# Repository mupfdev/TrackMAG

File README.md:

# TrackMAG

TrackMAG is an open source development board equipped with a
magnetometer, an accelerometer and a gyroscope and it is primarily
intended for the development of accessible input devices.

Details can be found on the [project
website](https://mupfdev.github.io/TrackMAG/).

# License

This project is, unless stated otherwise, licensed under the [CERN Open
Hardware Licence Version 2 -
Permissive](https://ohwr.org/cern_ohl_p_v2.txt).

MotionFX by STMicroelectronics is licenced under the terms of the SLA0077 Software License Agreement.  See the file
[SLA0077.pdf](pdf/SLA0077.pdf) for details.

[webdfu](https://github.com/devanlai/webdfu)</a> by Devan Lai is
licenced under the the [ISC
License](https://github.com/devanlai/webdfu/blob/gh-pages/LICENSE).

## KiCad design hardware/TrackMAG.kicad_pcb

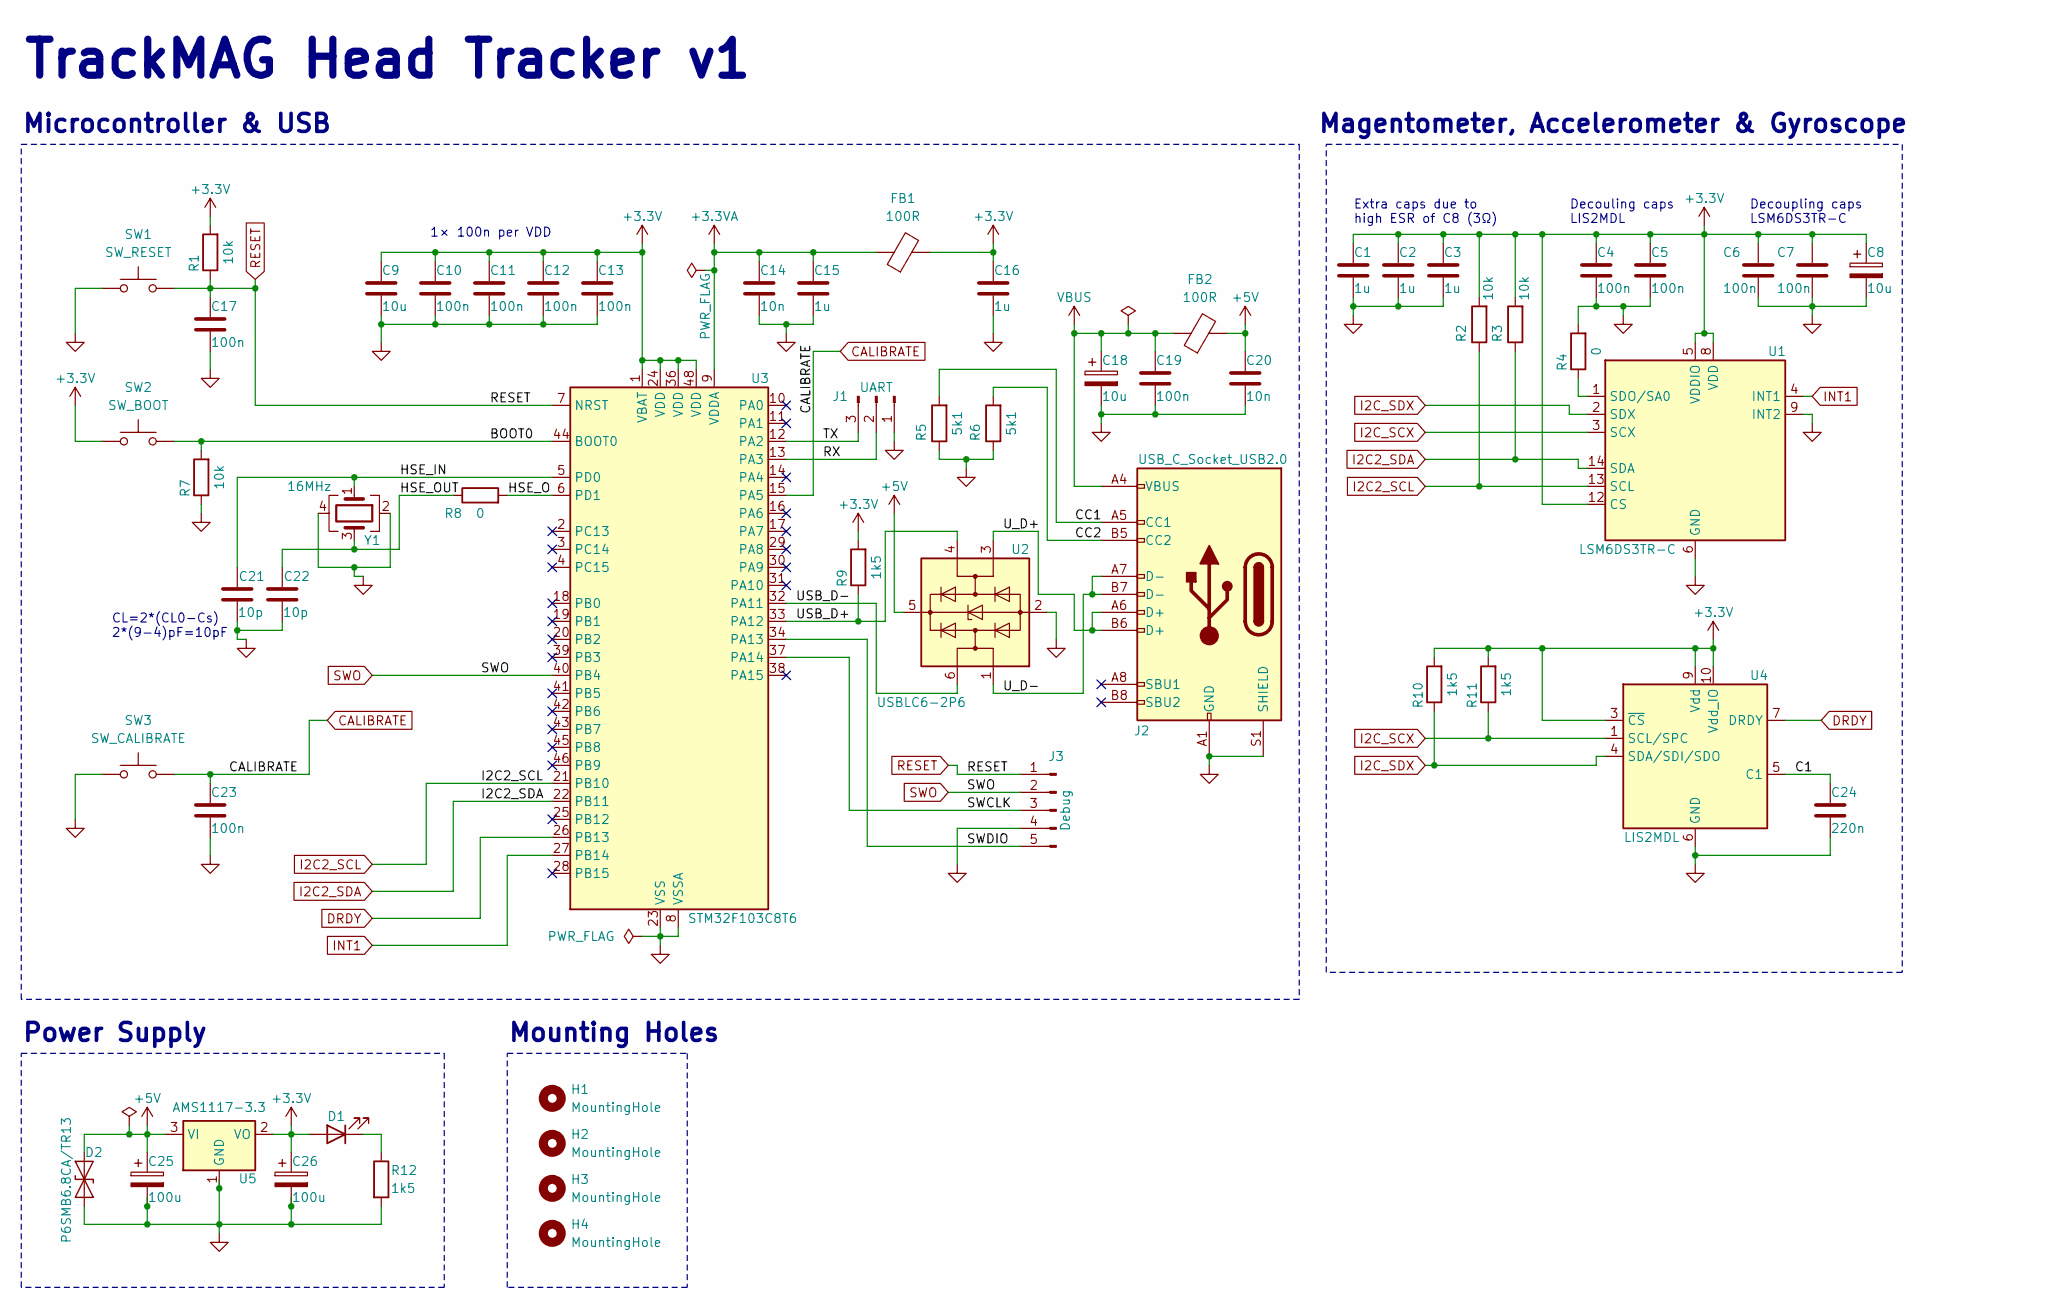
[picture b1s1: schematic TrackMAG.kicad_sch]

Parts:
C1, C2, C3, C15, C16: 1u; C_0402_1005Metric; JLCPCB Part # C52923
C4, C5, C6, C7, C10, C11, C12, C13, C17, C19, C23: 100n; C_0402_1005Metric; JLCPCB Part # C307331
C8, C18: 10u; CP_EIA-3216-18_Kemet-A; JLCPCB Part # C7171
C9: 10u; C_0402_1005Metric; JLCPCB Part # C15525
C14, C20: 10n; C_0402_1005Metric; JLCPCB Part # C15195
C21, C22: 10p; C_0402_1005Metric; JLCPCB Part # C32949
C24: 220n; C_0402_1005Metric; JLCPCB Part # C16772
C25, C26: 100u; CP_EIA-3528-21_Kemet-B; JLCPCB Part # C16133
D1: LED; LED_0603_1608Metric; JLCPCB Part # C2286
D2: P6SMB6.8CA/TR13; D_SMB; JLCPCB Part # C78395
FB1, FB2: 100R; R_0805_2012Metric; JLCPCB Part # C1015
H1, H2, H3, H4: MountingHole; MountingHole_2.1mm
J1: UART; PinHeader_1x03_P2.54mm_UART
J2: USB_C_Socket_USB2.0; USB_C_Receptacle_G-Switch_GT-USB-7010ASV; JLCPCB Part # C2988369
J3: Debug; PinHeader_1x05_P2.54mm_Debug
R1, R2, R3, R7: 10k; R_0402_1005Metric; JLCPCB Part # C25744
R4, R8: 0; R_0402_1005Metric; JLCPCB Part # C17168
R5, R6: 5k1; R_0402_1005Metric; JLCPCB Part # C25905
R9, R10, R11, R12: 1k5; R_0402_1005Metric; JLCPCB Part # C25867
SW1: SW_RESET; SW_Push_1P1T_XKB_TS-1187A_RESET; JLCPCB Part # C318884
SW2: SW_BOOT; SW_Push_1P1T_XKB_TS-1187A_BOOT; JLCPCB Part # C318884
SW3: SW_CALIBRATE; SW_Push_1P1T_XKB_TS-1187A_CALIBRATE; JLCPCB Part # C318884
U1: LSM6DS3TR-C; LGA-14_3x2.5mm_P0.5mm_LayoutBorder3x4y; JLCPCB Part # C967633
U2: USBLC6-2P6; SOT-666; JLCPCB Part # C2827693
U3: STM32F103C8T6; LQFP-48_7x7mm_P0.5mm; JLCPCB Part # C8734
U4: LIS2MDL; LGA-12_2x2mm_P0.5mm; JLCPCB Part # C919695
U5: AMS1117-3.3; SOT-223-3_TabPin2; JLCPCB Part # C6186
Y1: 16MHz; Crystal_SMD_3225-4Pin_3.2x2.5mm; JLCPCB Part # C13738

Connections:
+3.3V: C1.1, C2.1, C3.1, C4.1, C5.1, C6.1, C7.1, C8.1, C9.1, C10.1, C11.1, C12.1, C13.1, C16.1, C26.1, D1.2 (A), FB1.2, R1.2, R2.2, R3.2, R9.2, R10.2, R11.2, SW2.1, U1.5 (VDDIO), U1.8 (VDD), U1.12 (CS), U3.1 (VBAT), U3.24 (VDD), U3.36 (VDD), U3.48 (VDD), U4.3 (~CS), U4.9 (Vdd), U4.10 (Vdd_IO), U5.2 (VO)
+3.3VA: C14.1, C15.1, FB1.1, U3.9 (VDDA)
+5V: C20.1, C25.1, D2.1 (A1), FB2.2, U2.5 (VBUS), U5.3 (VI)
/BOOT0: R7.2, SW2.2, U3.44 (BOOT0)
/C1: C24.1, U4.5 (C1)
/CC1: J2.A5 (CC1), R5.2
/CC2: J2.B5 (CC2), R6.2
/HSE_IN: C21.1, U3.5 (PD0), Y1.1
/HSE_O: R8.2, U3.6 (PD1)
/HSE_OUT: C22.1, R8.1, Y1.3
/RX: J1.2, U3.13 (PA3)
/SWCLK: J3.3, U3.37 (PA14)
/SWDIO: J3.5, U3.34 (PA13)
/TX: J1.3, U3.12 (PA2)
/USB_D+: R9.1, U2.4 (I/O2), U3.33 (PA12)
/USB_D-: U2.6 (I/O1), U3.32 (PA11)
/U_D+: J2.A6 (D+), J2.B6 (D+), U2.3 (I/O2)
/U_D-: J2.A7 (D-), J2.B7 (D-), U2.1 (I/O1)
CALIBRATE: C23.1, SW3.2, U3.15 (PA5)
DRDY: U3.26 (PB13), U4.7 (DRDY)
GND: C1.2, C2.2, C3.2, C4.2, C5.2, C6.2, C7.2, C8.2, C9.2, C10.2, C11.2, C12.2, C13.2, C14.2, C15.2, C16.2, C17.2, C18.2, C19.2, C20.2, C21.2, C22.2, C23.2, C24.2, C25.2, C26.2, D2.2 (A2), J1.1, J2.A1 (GND), J2.A12 (GND), J2.B1 (GND), J2.B12 (GND), J2.S1 (SHIELD), J3.4, R4.2, R5.1, R6.1, R7.1, R12.2, SW1.1, SW3.1, U1.6 (GND), U1.7 (GND), U1.9 (INT2), U2.2 (GND), U3.8 (VSSA), U3.23 (VSS), U3.35 (VSS), U3.47 (VSS), U4.6 (GND), U4.8 (GND), U5.1 (GND), Y1.2, Y1.4
I2C2_SCL: R2.1, U1.13 (SCL), U3.21 (PB10)
I2C2_SDA: R3.1, U1.14 (SDA), U3.22 (PB11)
I2C_SCX: R11.1, U1.3 (SCX), U4.1 (SCL/SPC)
I2C_SDX: R10.1, U1.2 (SDX), U4.4 (SDA/SDI/SDO)
INT1: U1.4 (INT1), U3.27 (PB14)
unnamed: D1.1 (K), R12.1
unnamed: R4.1, U1.1 (SDO/SA0)
RESET: C17.1, J3.1, R1.1, SW1.2, U3.7 (NRST)
SWO: J3.2, U3.40 (PB4)
VBUS: C18.1, C19.1, FB2.1, J2.A4 (VBUS), J2.A9 (VBUS), J2.B4 (VBUS), J2.B9 (VBUS)

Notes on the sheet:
Microcontroller & USB
Power Supply
TrackMAG Head Tracker v1
1× 100n per VDD
CL=2*(CL0-Cs) 2*(9-4)pF=10pF
Decoupling caps LSM6DS3TR-C
Decouling caps LIS2MDL
Magentometer, Accelerometer & Gyroscope
Mounting Holes
Extra caps due to high ESR of C8 (3Ω)

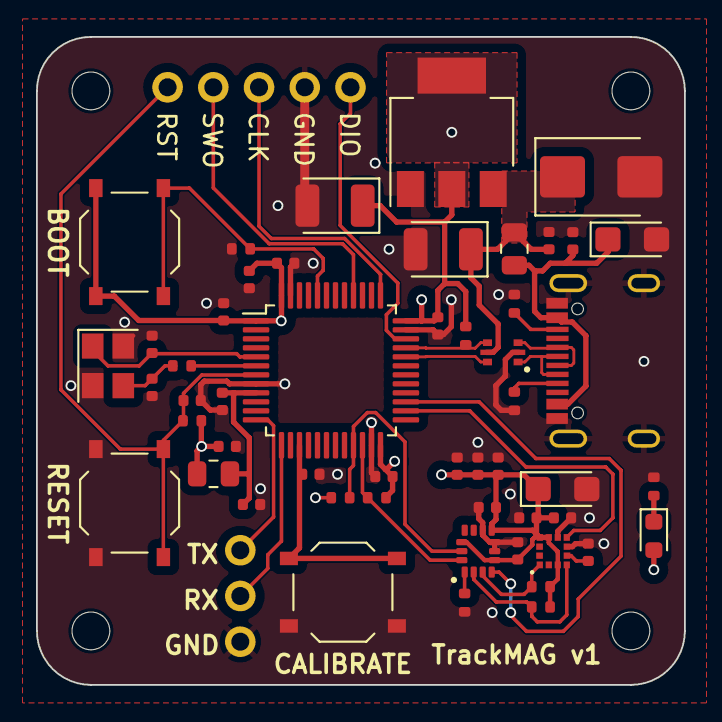
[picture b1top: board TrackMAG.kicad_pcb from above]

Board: 4 copper layers, 36.0 x 36.0 mm, 58 parts (0 on the bottom side), 31 nets.

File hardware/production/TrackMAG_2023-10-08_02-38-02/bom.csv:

Designator,Footprint,Quantity,Value,LCSC Part #
"C1, C15, C16, C2, C3",0402,5,1u,C52923
"C10, C11, C12, C13, C17, C19, C23, C4, C5, C6, C7",0402,11,100n,C307331
"C14, C20",0402,2,10n,C15195
"C18, C8",CP_EIA-3216-18_Kemet-A,2,10u,C7171
"C21, C22",0402,2,10p,C32949
C24,0402,1,220n,C16772
"C25, C26",CP_EIA-3528-21_Kemet-B,2,100u,C16133
C9,0402,1,10u,C15525
D1,0603,1,LED,C2286
D2,D_SMB,1,P6SMB6.8CA,C78395
"FB1, FB2",0805,2,100R,C1015
J2,USB_C_Receptacle_G-Switch_GT-USB-7010ASV,1,USB_C_Socket_USB2.0,C2988369
"R1, R2, R3, R7",0402,4,10k,C25744
"R10, R11, R12, R9",0402,4,1k5,C25867
"R4, R8",0402,2,0,C17168
"R5, R6",0402,2,5k1,C25905 
SW1,SW_Push_1P1T_XKB_TS-1187A_RESET,1,SW_RESET,C318884
SW2,SW_Push_1P1T_XKB_TS-1187A_BOOT,1,SW_BOOT,C318884
SW3,SW_Push_1P1T_XKB_TS-1187A_CALIBRATE,1,SW_CALIBRATE,C318884
U1,LGA-14_3x2.5mm_P0.5mm_LayoutBorder3x4y,1,LSM6DS3TR-C,C967633
U2,SOT-666,1,USBLC6-2P6,C2827693
U3,LQFP-48_7x7mm_P0.5mm,1,STM32F103C8T6,C8734
U4,LGA-12_2x2mm_P0.5mm,1,LIS2MDL,C919695
U5,SOT-223-3_TabPin2,1,AMS1117-3.3,C6186
Y1,Crystal_SMD_3225-4Pin_3.2x2.5mm,1,16MHz, C13738

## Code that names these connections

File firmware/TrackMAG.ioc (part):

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Mcu.Name=STM32F103C(8-B)Tx
Mcu.Package=LQFP48
Mcu.UserName=STM32F103C8Tx
PA11.Mode=Device
PA11.Signal=USB_DM
PA12.Mode=Device
PA12.Signal=USB_DP
PA13.Mode=Serial_Wire
PA13.Signal=SYS_JTMS-SWDIO
PA14.Mode=Serial_Wire
PA14.Signal=SYS_JTCK-SWCLK
PA2.Mode=Asynchronous
PA2.Signal=USART2_TX
PA3.Mode=Asynchronous
PA3.Signal=USART2_RX
PA5.GPIOParameters=GPIO_PuPd,GPIO_Label,GPIO_ModeDefaultEXTI
PA5.GPIO_Label=CALIBRATE
PA5.GPIO_ModeDefaultEXTI=GPIO_MODE_IT_RISING_FALLING
PA5.GPIO_PuPd=GPIO_PULLUP
PA5.Signal=GPXTI5
PB10.Mode=I2C
PB10.Signal=I2C2_SCL
PB11.Mode=I2C
PB11.Signal=I2C2_SDA
PB13.GPIOParameters=GPIO_PuPd,GPIO_Label,GPIO_ModeDefaultEXTI
PB13.GPIO_Label=DRDY
PB13.GPIO_ModeDefaultEXTI=GPIO_MODE_IT_RISING
PB13.GPIO_PuPd=GPIO_PULLDOWN
PB13.Signal=GPXTI13
PB14.GPIOParameters=GPIO_Label,GPIO_ModeDefaultEXTI
PB14.GPIO_Label=INT1
PB14.GPIO_ModeDefaultEXTI=GPIO_MODE_IT_RISING
PB14.Signal=GPXTI14
PD0-OSC_IN.Mode=HSE-External-Oscillator
PD0-OSC_IN.Signal=RCC_OSC_IN
PD1-OSC_OUT.Mode=HSE-External-Oscillator
PD1-OSC_OUT.Signal=RCC_OSC_OUT
RCC.HSEDivPLL=RCC_HSE_PREDIV_DIV2
RCC.HSE_VALUE=16000000
RCC.SYSCLKFreq_VALUE=72000000
RCC.SYSCLKSource=RCC_SYSCLKSOURCE_PLLCLK
board=custom

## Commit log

2023-10-02 Add firmware base project
2023-10-02 Update pinout to match current firmware configuration
2023-10-04 Backup current progress
2023-10-04 Update schematic to match current progress
2023-10-06 Backup currend KiCAD progress
2023-10-06 Add ground planes
2023-10-06 Add missing connections
2023-10-06 Add reference vias
2023-10-06 Cleanup
2023-10-06 Update schematic PDF and minor PCB cleanup
2023-10-06 Center PCB
2023-10-06 Update PDF schematic, add calibrate switch
2023-10-06 Add calibrate switch
2023-10-06 Update base firmware configuration to match current hardware setup
2023-10-07 Fix various problems, cleanup after review
2023-10-07 Minor cleanup
2023-10-07 Remove redundant connection on PB0
2023-10-07 Adjust firmware accordingly, remove setting for PB0
2023-10-07 Remove redundant vias, adjust reference vias
2023-10-07 Optimize PCB layout
2023-10-07 Increase spacing of INT1 line
2023-10-08 Remove UART pin header from position files
2023-10-08 Hide pin header 3D models
2023-10-08 Final cleanup v1
2023-10-08 Add v1 production files used for JLCPCB order
2023-10-11 Minor cleanup, adjust wrong symbol in schematic and adjust TV footprint on PCB
2023-10-11 Add work-in-progress project case
2023-10-12 Add folder: gh-pages
2023-10-12 Move index.html from gh-pages to docs
2023-10-12 Add yet unfinished TrackMAG case to GitHub pages
2023-10-12 Update yet unfinished case 3D model
2023-10-12 Attempt to fix WebGL rendering by fixing load errors
2023-10-12 Move PDFs to dedicated directory, docs is reserved for GitHub pages
2023-10-13 Recreate yet-unfinished case design, lid and snap-fit joint
2023-10-14 Replace snap-fit with simpler press-fit design
2023-10-14 Add yet untested twist-lock for headset mount
2023-10-15 Update mount material for better visibility
2023-10-15 Update project website to fit mupf.dev design
2023-10-15 Update stylesheet links
2023-10-15 Update content type
2023-10-15 Update project description
2023-10-16 Update project website
2023-10-16 Add schematic to project website
2023-10-16 Add basic license
2023-10-16 Add remark regarding flyLILLO ETS
2023-10-18 Add 3D rendering of PCB
2023-10-18 Add missing script
2023-10-18 Add missing html tag
2023-10-18 Enable mobile version of magnifier js
2023-10-18 Update case
2023-10-18 Just making sure everything is up to date
2023-10-19 Optimise case, add buttons
2023-10-19 Add yet unmodified, non-working USB DFU bootloader
2023-10-19 Adjust bootloader vid/pid, update clock configuration to use 16MHz oscillator
2023-10-19 Add webdfu
2023-10-19 Add webdfu.html for testing
2023-10-19 More DFU util debugging
2023-10-19 Add original form code to check whether it is working correctly
2023-10-19 webdfu debugging: remove one thing at a time
2023-10-19 Cosmetic changes, remove redundant button
2023-10-19 Fix error, update vid list
2023-10-19 Fix error?
2023-10-19 bootloader, minor cleanup
2023-10-19 Fix html syntax
2023-10-20 Update index.html: hide Detach DFU button
2023-10-20 Add buttons, minor modifications on case
2023-10-20 Update phrasing
2023-10-20 Update colors for better contrast
2023-10-20 Rework case to be able to strap it to a headset without the optional twist lock mechanism
2023-10-20 Add prototype image
2023-10-20 Add updated model
2023-10-20 Fix path to js, add minimal lightbox script
2023-10-20 Add contents link to prototype section
2023-10-20 Update date
2023-10-20 Prototype: make background transparent
2023-10-20 Replace prototype image because it looks weird, add 3 new images
2023-10-20 Fix typo
2023-10-20 Add css class to gallery
2023-10-20 Update description
2023-10-21 Update phrasing, change licence terms
2023-10-22 Firmware: add basic, XAC-compatible USB-HID support
2023-10-22 Rename HID profile to make clear that it works with the XAC
2023-10-22 Poll sensor data
2023-10-22 Close comment
2023-10-26 Add basic filtering, implement pitch
2023-10-26 Add GitHub actions workflow to build firmware
2023-10-26 Copy workflow to designated directory
2023-10-26 Add status badge
2023-10-26 Update pipeline name
2023-10-26 Fix typos
2023-10-27 Add AN3192
2023-10-27 Add design tip docs by ST
2023-10-28 Remove FreeRTOS, add MotionFX, adjust code accordingly, yet not functional
2023-10-29 Rewrite MAG handler, initialise sensors from scratch, yet unfinished because the calculated yaw axis (MotionFX) seems extremely unstable.
2023-10-30 Apply filter chain
2023-10-30 Disable automatic gbias calculation, calibration only
2023-10-30 Add slightly adjusted linker scripts, setup MotionFX properly - works now, add calibration feature
2023-10-31 Save calibration data to flash, load it on bootup
2023-10-31 Update GitHub actions workflow to patch firmware header (test), minor firmware cleanup
2023-10-31 Fix typo, adjust workflow to only run when the firmware code has been updated
2023-10-31 Update workflow
2023-10-31 Test workflow
2023-10-31 Fix path in workflow
2023-10-31 Adjust file name of output binary
2023-10-31 Adjust binary file name
2023-10-31 Test workflow adjustment
2023-10-31 Adjust workflow
2023-10-31 Fix error in workflow
2023-10-31 Upload firmware binary to project website
2023-10-31 Add link to latest firmware
2023-10-31 Output orientation string via UART
2023-10-31 Add firmware build status badge
2023-10-31 Move badge to status section
2023-10-31 Reorganise
2023-10-31 Update formatting
2023-10-31 Reorganise elements
2023-11-01 Use 0 for default calibration when stored value is not a number, eg when flash is empty
2023-11-01 Drop polling, use interrupts
2023-11-01 Bring everything into scale
2023-11-02 Add section: data visualisation
2023-11-02 Update phrasing, add link
2023-11-02 Update licence information
2023-11-02 Whoops, this isn't markdown
2023-11-02 Add bootloader test workflow
2023-11-02 Trigger workflow
2023-11-02 Update bootloader workflow
2023-11-02 Update workflows, set flash size in bootloader Makefile
2023-11-02 Fix workflow
2023-11-02 Add workflow badge, adjust bootloader workflow
2023-11-02 Commit from GitHub Actions (bootloader)
2023-11-02 Add paragraph
2023-11-02 Add bootloader workflow badge
2023-11-02 Remove duplicate badges entirely, looks better that way
2023-11-03 Build Release instead of Debug configuration
2023-11-03 Test updated firmware workflow
2023-11-03 Adjust flash size, apparently the bootloader stopped working properly?
2023-11-03 Add hack to be able to use USB without replugging
2023-11-03 Commit from GitHub Actions (firmware)
2023-11-03 Reduce flash size again
2023-11-03 Add reference manual
2023-11-03 Rename function to avoid confusion
2023-11-04 Update debug/launch configurations to use upper flash bank (which isn't officially supported)
2023-11-04 Disable writeprotection in bootloader
2023-11-04 Rename mag_handler
2023-11-05 Add basic CMake configuration; does not work yet - resulting .text does not fit in region FLASH
2023-11-05 Add build configuration for continous integration
2023-11-05 Add licence information
2023-11-05 Update build configurations to fix workflow
2023-11-05 Fix CMake configuration
2023-11-05 Compile with -flto
2023-11-05 Minor CMake cleanup
2023-11-09 Add additional build config, add x axis transformation
2023-11-12 Add .nojekyll file
